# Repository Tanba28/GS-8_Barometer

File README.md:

# GS-8_Barometer
GS-8 Barometer Board

Master project -> [project-arrows/GS-8](https://github.com/project-arrows/GS-8)

## Overview
 * GS-8気圧ロガー

## Role
 * 気圧をロギングする。
 * 頂点検知を行う。
 * 頂点検知結果を[開放基板](https://github.com/Tanba28/GS-8_PD_Board)に伝達する。

## Link
 * [Tanba28/GS-8_PM_Board](https://github.com/Tanba28/GS-8_PM_Board)
 * [Tanba28/GS-8_PD_Board](https://github.com/Tanba28/GS-8_PD_Board)
 * [Tanba28/GS-8_Motion_Logger](https://github.com/Tanba28/GS-8_Motion_Logger)
 * [Tanba28/GS-8_Relay_Board](https://github.com/Tanba28/GS-8_Relay_Board)
 * [ringo156/GS-8_ACCLRM_Board](https://github.com/ringo156/GS-8_ACCLRM_Board)
 * [takamasavvv/RCT-X_Logger](https://github.com/takamasavvv/RCT-X-Logger)
 * [takamasavvv/RCT-X-Telemetry](https://github.com/takamasavvv/RCT-X-Telemetry)
 
## LICENSE
MIT License

Copyright (c) 2019 Tanba28

Permission is hereby granted, free of charge, to any person obtaining a copy
of this software and associated documentation files (the "Software"), to deal
in the Software without restriction, including without limitation the rights
to use, copy, modify, merge, publish, distribute, sublicense, and/or sell
copies of the Software, and to permit persons to whom the Software is
furnished to do so, subject to the following conditions:

The above copyright notice and this permission notice shall be included in all
copies or substantial portions of the Software.

THE SOFTWARE IS PROVIDED "AS IS", WITHOUT WARRANTY OF ANY KIND, EXPRESS OR
IMPLIED, INCLUDING BUT NOT LIMITED TO THE WARRANTIES OF MERCHANTABILITY,
FITNESS FOR A PARTICULAR PURPOSE AND NONINFRINGEMENT. IN NO EVENT SHALL THE
AUTHORS OR COPYRIGHT HOLDERS BE LIABLE FOR ANY CLAIM, DAMAGES OR OTHER
LIABILITY, WHETHER IN AN ACTION OF CONTRACT, TORT OR OTHERWISE, ARISING FROM,
OUT OF OR IN CONNECTION WITH THE SOFTWARE OR THE USE OR OTHER DEALINGS IN THE
SOFTWARE.

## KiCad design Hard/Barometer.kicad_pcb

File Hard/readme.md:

# GS-8_Barometer
GS-8 Barometer Board

## BOM
|Reference| Quantity| Datasheet| Agency| Link| MPN|
|:-:|:-:|:-:|:-:|:-:|:-:|
|C11 C12 |2|https://search.murata.co.jp/Ceramy/image/img/A01X/G101/ENG/GRM1555C1H9R0DA01-01.pdf|Digkey|https://www.digikey.jp/product-detail/ja/murata-electronics/GRM1555C1H9R0DA01D/490-5880-1-ND/3175209|GRM1555C1H9R0DA01D|
|C1 C10 C13 C15 C16 C17 C18 C9 |8|https://search.murata.co.jp/Ceramy/image/img/A01X/G101/ENG/GRM155R61E105KA12-01.pdf|Digikey|https://www.digikey.jp/product-detail/ja/murata-electronics/GRM155R61E105KA12D/490-10017-1-ND/5026367|GRM155R61E105KA12D|
|C25 |1|https://search.murata.co.jp/Ceramy/image/img/A01X/G101/ENG/GRM155R71H472KA01-01.pdf|Digikey|https://www.digikey.jp/product-detail/ja/murata-electronics/GRM155R71H472KA01D/490-1308-1-ND/587946|GRM155R71H472KA01D|
|C14 C2 C26 C27 C29 C3 C30 C4 C5 C6 C7 C8 |12|https://search.murata.co.jp/Ceramy/image/img/A01X/G101/ENG/GRM155R62A104KE14-01.pdf|Digikey|https://www.digikey.jp/product-detail/ja/murata-electronics/GRM155R62A104KE14D/490-10458-1-ND/5026370|GRM155R62A104KE14D|
|C28 |1|https://search.murata.co.jp/Ceramy/image/img/A01X/G101/ENG/GRM188R6YA106MA73-01.pdf|akizuki|http://akizukidenshi.com/catalog/g/gP-13161/|GRM188R6YA106MA73D|
|D1 |1|~||||
|D2 |1|~||||
|D3 |1|~||||
|D4 D5 |2|http://akizukidenshi.com/download/ds/rohm/rsx101vam30-j.pdf|akizuki|http://akizukidenshi.com/catalog/g/gI-05951/|RSX101VAM-30TR|
|J2 |1|http://www.jst-mfg.com/product/pdf/eng/eJQ.pdf|Digikey|https://www.digikey.jp/products/ja?keywords=05JQ-BT|05JQ-BT|
|J3 |1|https://www.hirose.com/product/document?clcode=CL0242-0056-3-30&productname=ZX62D-B-5PA8(30)&series=ZX&documenttype=Catalog&lang=en&documentid=D31704_en|Digikey|https://www.digikey.jp/product-detail/ja/hirose-electric-co-ltd/ZX62D-B-5P8-30/H125272CT-ND/5994758|ZX62D-B-5P8(30)|
|J4 |1|http://download.siliconexpert.com/pdfs/2014/12/9/8/14/1/458/jst_/manual/29exh.pdf|Digikey|https://www.digikey.jp/product-detail/ja/jst-sales-america-inc/S4B-XH-A-LF-SN/455-2243-ND/1651041|S4B-XH-A|
|R1 R2 R3 |3|https://b2b-api.panasonic.eu/file_stream/pids/fileversion/1242|Digikey|https://www.digikey.jp/product-detail/ja/panasonic-electronic-components/ERJ-2GEJ102X/P1.0KJCT-ND/146897|ERJ-2GEJ102X|
|R11 R12 |2|https://b2b-api.panasonic.eu/file_stream/pids/fileversion/1242|Digkey|https://www.digikey.jp/product-detail/ja/panasonic-electronic-components/ERJ-2GEJ560X/P56JCT-ND/147039|ERJ-2GEJ560X|
|R4 R5 |2|https://b2b-api.panasonic.eu/file_stream/pids/fileversion/1242|Digikey|https://www.digikey.jp/product-detail/ja/panasonic-electronic-components/ERJ-2GEJ220X/P22JCT-ND/146937|ERJ-2GEJ220X|
|R10 R13 R14 R15 R16 R6 R7 R8 R9 |9|https://industrial.panasonic.com/cdbs/www-data/pdf/RDA0000/AOA0000C304.pdf|Digikey|https://www.digikey.jp/product-detail/ja/panasonic-electronic-components/ERJ-2RKF2202X/P22.0KLCT-ND/1746653|ERJ-2RKF2202X|
|U1 |1|https://www.cypress.com/file/45906/download|Digikey|https://www.digikey.jp/product-detail/ja/cypress-semiconductor-corp/CY8C5888LTQ-LP097/2015-CY8C5888LTQ-LP097-ND/9955055|CY8C5868LTI-LP039|
|U2 |1|http://www.winbond.com/resource-files/w25n01gv%20revl%20050918%20unsecured.pdf|Digikey|https://www.digikey.jp/product-detail/ja/winbond-electronics/W25N01GVZEIG-TR/W25N01GVZEIGCT-ND/7393545|W25N01GVZEIG TR|
|U3 |1|https://www.onsemi.com/pub/Collateral/NCV7342-D.PDF|Digikey|https://www.digikey.jp/product-detail/ja/on-semiconductor/NCV7342MW3R2G/NCV7342MW3R2GOSCT-ND/8538664|NCV7342MW3R2G|
|U4 |1|www.st.com/resource/en/datasheet/lps25hb.pdf|Digikey|https://www.digikey.jp/product-detail/ja/stmicroelectronics/LPS22HBTR/497-16265-1-ND/5799917|LPS22HB|
|VR1 |1|https://www.onsemi.com/pub/Collateral/NCP718-D.PDF|Digikey|https://www.digikey.jp/product-detail/ja/on-semiconductor/NCP718ASN500T1G/NCP718ASN500T1GOSCT-ND/9749423|NCP718ASN500T1G|
|VR2 |1|https://www.onsemi.com/pub/Collateral/NCP718-D.PDF|Digikey|https://www.digikey.jp/product-detail/ja/on-semiconductor/NCP718ASN330T1G/NCP718ASN330T1GOSCT-ND/9749422|NCP718ASN330T1G|
|Y1 |1|https://www.murata.com/~/media/webrenewal/products/timingdevice/crystalu/flyers/vppt-hcrj078-d.ashx?la=en-us|Digikey|https://www.digikey.jp/product-detail/ja/murata-electronics/XRCHA24M000F0A01R0/490-9652-1-ND/4930056|XRCHA24M000F0A01R0|
||

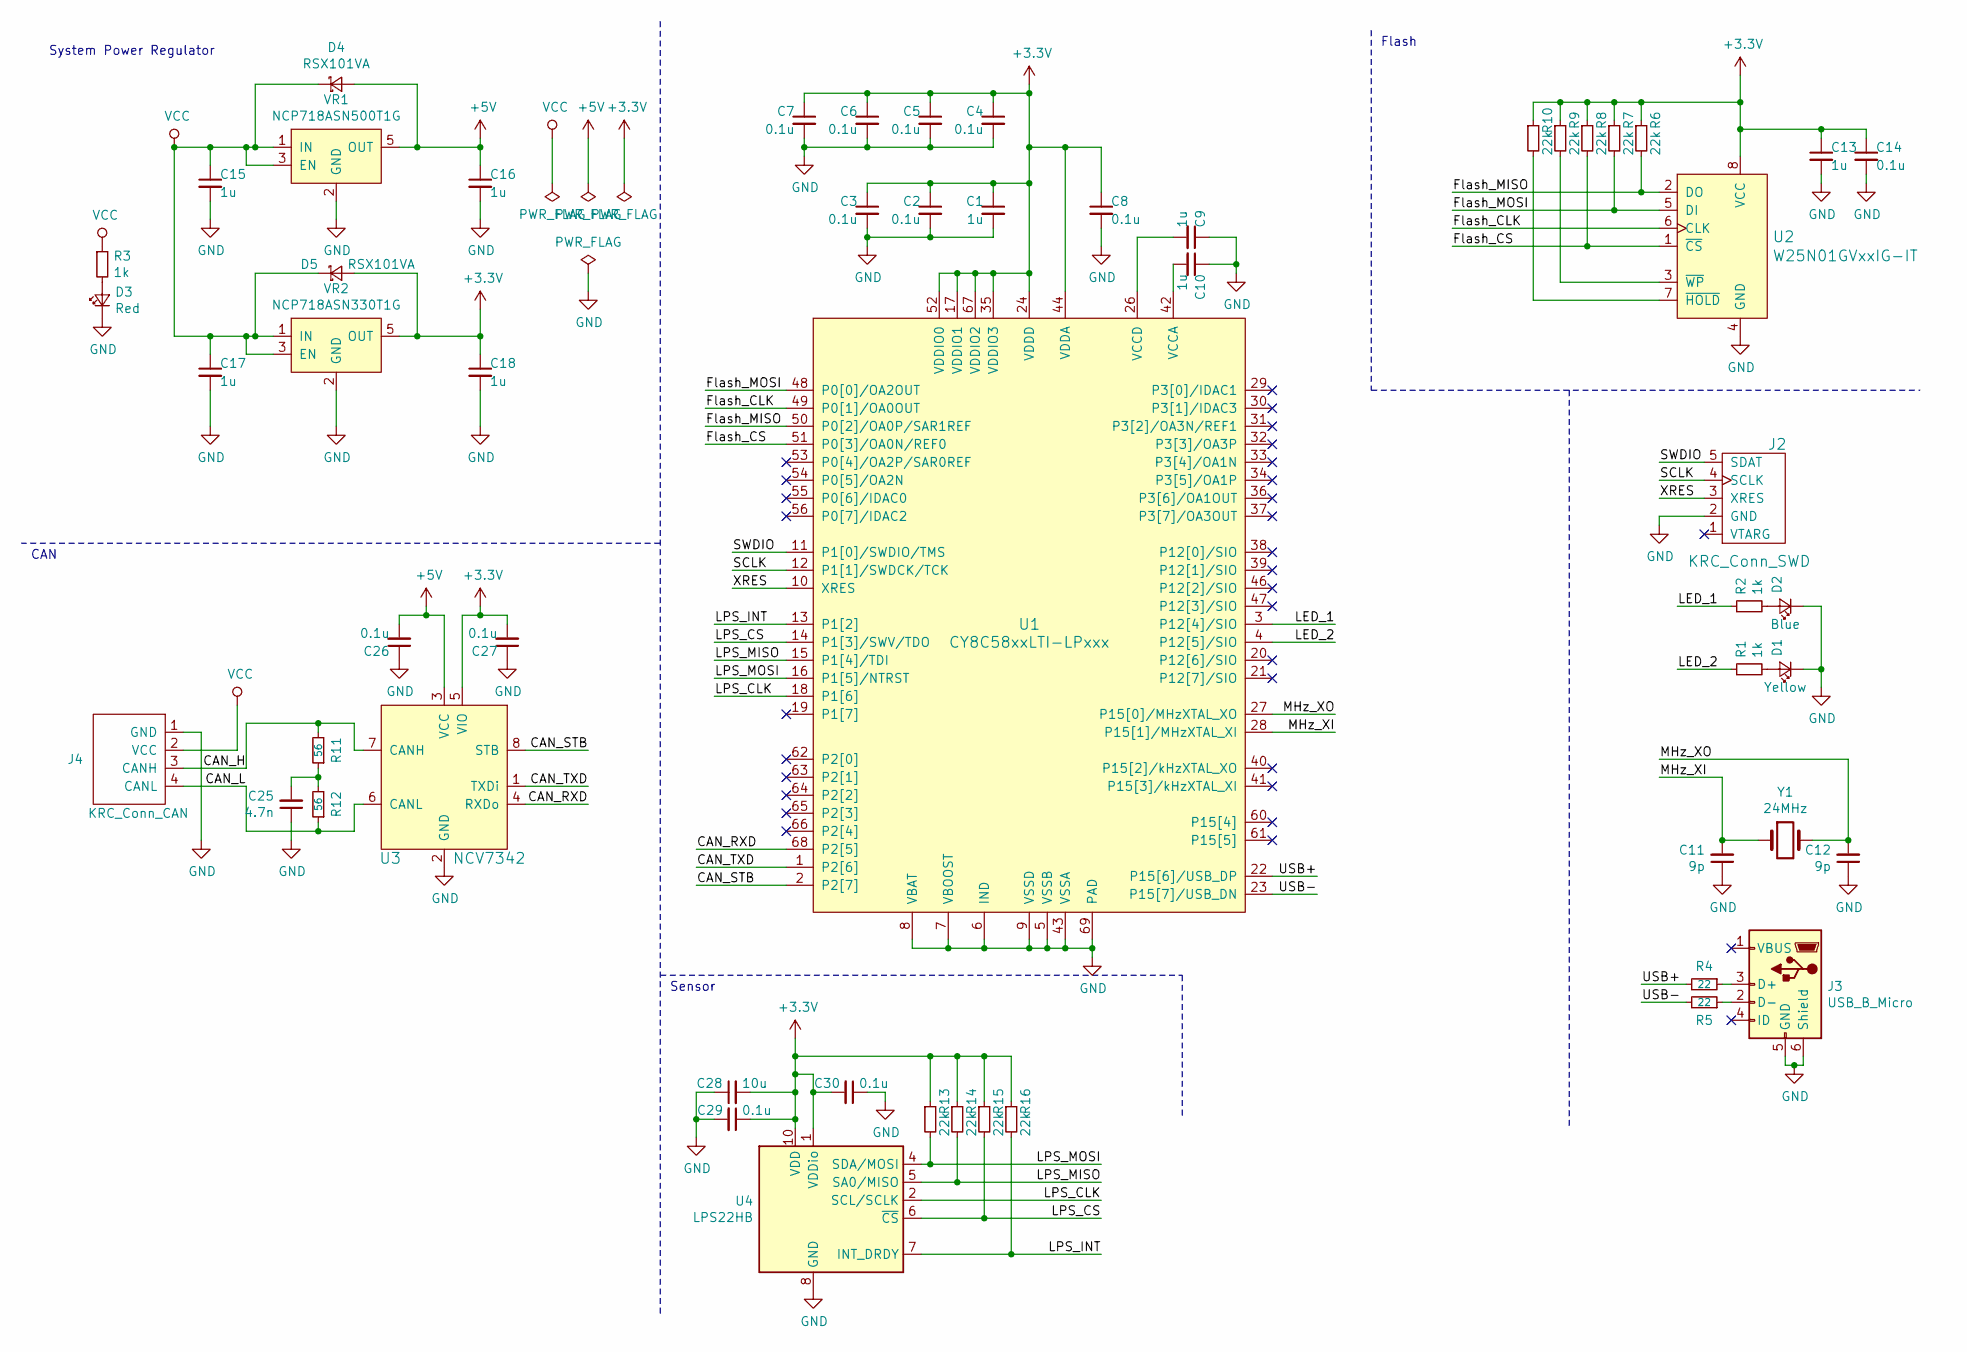
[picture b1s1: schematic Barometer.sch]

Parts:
C1, C9, C10, C13, C15, C16, C17, C18: 1u; C_0402_1005Metric; MPN GRM155R61E105KA12D
C2, C3, C4, C5, C6, C7, C8, C14, C26, C27, C29, C30: 0.1u; C_0402_1005Metric; MPN GRM155R62A104KE14D
C11, C12: 9p; C_0402_1005Metric; MPN GRM1555C1H9R0DA01D
C25: 4.7n; C_0402_1005Metric; MPN GRM155R71H472KA01D
C28: 10u; C_0603_1608Metric; MPN GRM188R6YA106MA73D
D1: Yellow; LED_0603_1608Metric
D2: Blue; LED_0603_1608Metric
D3: Red; LED_0603_1608Metric
D4, D5: RSX101VA; D_TUMD2; MPN RSX101VAM-30TR
J2: KRC_Conn_SWD; JST_JQ_05JQ-BT_1x05_P2.5mm_Vertical; MPN 05JQ-BT
J3: USB_B_Micro; Hirose_ZX_ZX62D-B-5P8; MPN ZX62D-B-5P8(30)
J4: KRC_Conn_CAN; JST_XH_S4B-XH-A_1x04_P2.50mm_Horizontal; MPN S4B-XH-A
R1, R2, R3: 1k; R_0402_1005Metric; MPN ERJ-2GEJ102X
R4, R5: 22; R_0402_1005Metric; MPN ERJ-2GEJ220X
R6, R7, R8, R9, R10, R13, R14, R15, R16: 22k; R_0402_1005Metric; MPN ERJ-2RKF2202X
R11, R12: 56; R_0402_1005Metric; MPN ERJ-2GEJ560X
U1: CY8C58xxLTI-LPxxx; Cypress_QFN-68_EP_8x8_Pitch0.4mm; MPN CY8C5868LTI-LP039
U2: W25N01GVxxIG-IT; WSON-8_8x6mm_P1.27mm; MPN W25N01GVZEIG TR
U3: NCV7342; DFN-8-1EP_3x3mm_P0.65mm_EP1.55x2.4mm; MPN NCV7342MW3R2G
U4: LPS22HB; ST_HLGA-10_2.5x2.5mm_P0.6mm_LayoutBorder3x2y; MPN LPS22HB
VR1: NCP718ASN500T1G; TSOT-23-5; MPN NCP718ASN500T1G
VR2: NCP718ASN330T1G; TSOT-23-5; MPN NCP718ASN330T1G
Y1: 24MHz; Crystal_Murata_XRCHA; MPN XRCHA24M000F0A01R0

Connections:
+3V3: C1.1, C2.1, C3.1, C4.1, C5.1, C6.1, C7.1, C8.1, C13.1, C14.1, C18.1, C27.2, C28.2, C29.1, C30.2, D5.2 (A), R6.1, R7.1, R8.1, R9.1, R10.1, R13.1, R14.1, R15.1, R16.1, U1.17 (VDDIO1), U1.24 (VDDD), U1.35 (VDDIO3), U1.44 (VDDA), U1.52 (VDDIO0), U1.59 (VDDD), U1.67 (VDDIO2), U2.8 (VCC), U3.5 (VIO), U4.1 (VDDio), U4.10 (VDD), VR2.5 (OUT)
+5V: C16.1, C26.2, D4.2 (A), U3.3 (VCC), VR1.5 (OUT)
/CAN_H: J4.3 (CANH), R11.2, U3.7 (CANH)
/CAN_L: J4.4 (CANL), R12.1, U3.6 (CANL)
/CAN_RXD: U1.68 (P2[5]), U3.4 (RXDo)
/CAN_STB: U1.2 (P2[7]), U3.8 (STB)
/CAN_TXD: U1.1 (P2[6]), U3.1 (TXDi)
/Flash_CLK: U1.49 (P0[1]/OA0OUT), U2.6 (CLK)
/Flash_CS: R8.2, U1.51 (P0[3]/OA0N/REF0), U2.1 (~CS)
/Flash_MISO: R6.2, U1.50 (P0[2]/OA0P/SAR1REF), U2.2 (DO)
/Flash_MOSI: R7.2, U1.48 (P0[0]/OA2OUT), U2.5 (DI)
/LED_1: R2.1, U1.3 (P12[4]/SIO)
/LED_2: R1.1, U1.4 (P12[5]/SIO)
/LPS_CLK: U1.18 (P1[6]), U4.2 (SCL/SCLK)
/LPS_CS: R15.2, U1.14 (P1[3]/SWV/TDO), U4.6 (~CS)
/LPS_INT: R16.2, U1.13 (P1[2]), U4.7 (INT_DRDY)
/LPS_MISO: R14.2, U1.15 (P1[4]/TDI), U4.5 (SA0/MISO)
/LPS_MOSI: R13.2, U1.16 (P1[5]/NTRST), U4.4 (SDA/MOSI)
/MHz_XI: C11.2, U1.28 (P15[1]/MHzXTAL_XI), Y1.1
/MHz_XO: C12.2, U1.27 (P15[0]/MHzXTAL_XO), Y1.2
/SCLK: J2.4 (SCLK), U1.12 (P1[1]/SWDCK/TCK)
/SWDIO: J2.5 (SDAT), U1.11 (P1[0]/SWDIO/TMS)
/USB+: R4.2, U1.22 (P15[6]/USB_DP)
/USB-: R5.2, U1.23 (P15[7]/USB_DN)
/XRES: J2.3 (XRES), U1.10 (XRES)
GND: C1.2, C2.2, C3.2, C4.2, C5.2, C6.2, C7.2, C8.2, C9.1, C10.1, C11.1, C12.1, C13.2, C14.2, C15.2, C16.2, C17.2, C18.2, C25.1, C26.1, C27.1, C28.1, C29.2, C30.1, D1.1 (K), D2.1 (K), D3.1 (K), J2.2 (GND), J3.5 (GND), J3.6 (Shield), J4.1 (GND), U1.5 (VSSB), U1.6 (IND), U1.7 (VBOOST), U1.8 (VBAT), U1.9 (VSSD), U1.25 (VSSD), U1.43 (VSSA), U1.45 (VSSD), U1.58 (VSSD), U1.69 (PAD), U2.4 (GND), U2.9, U3.2 (GND), U3.9, U4.3 (GND), U4.8 (GND), U4.9 (GND), VR1.2 (GND), VR2.2 (GND)
unnamed: C9.2, U1.26 (VCCD), U1.57 (VCCD)
unnamed: C10.2, U1.42 (VCCA)
unnamed: C25.2, R11.1, R12.2
unnamed: D1.2 (A), R1.2
unnamed: D2.2 (A), R2.2
unnamed: D3.2 (A), R3.2
unnamed: J3.2 (D-), R5.1
unnamed: J3.3 (D+), R4.1
unnamed: R9.2, U2.3 (~WP)
unnamed: R10.2, U2.7 (~HOLD)
VCC: C15.1, C17.1, D4.1 (K), D5.1 (K), J4.2 (VCC), R3.1, VR1.1 (IN), VR1.3 (EN), VR2.1 (IN), VR2.3 (EN)

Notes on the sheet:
System Power Regulator
Flash
Sensor
CAN

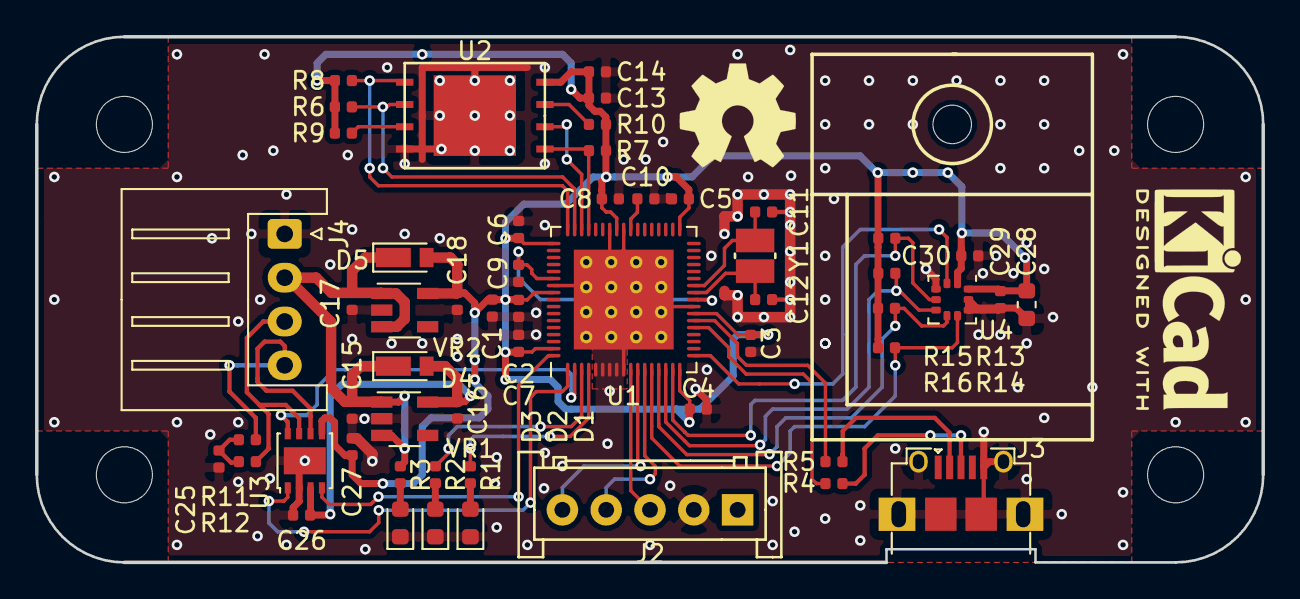
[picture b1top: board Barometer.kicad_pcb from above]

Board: 2 copper layers, 70.0 x 30.0 mm, 55 parts (0 on the bottom side), 37 nets.

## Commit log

2019-10-12 [add] ハード完成。ガーバ出力
2019-10-12 [update] 回路図のフィールドを編集
2019-10-12 [update] READMEを整備
2019-10-12 [add] READMEを整備
